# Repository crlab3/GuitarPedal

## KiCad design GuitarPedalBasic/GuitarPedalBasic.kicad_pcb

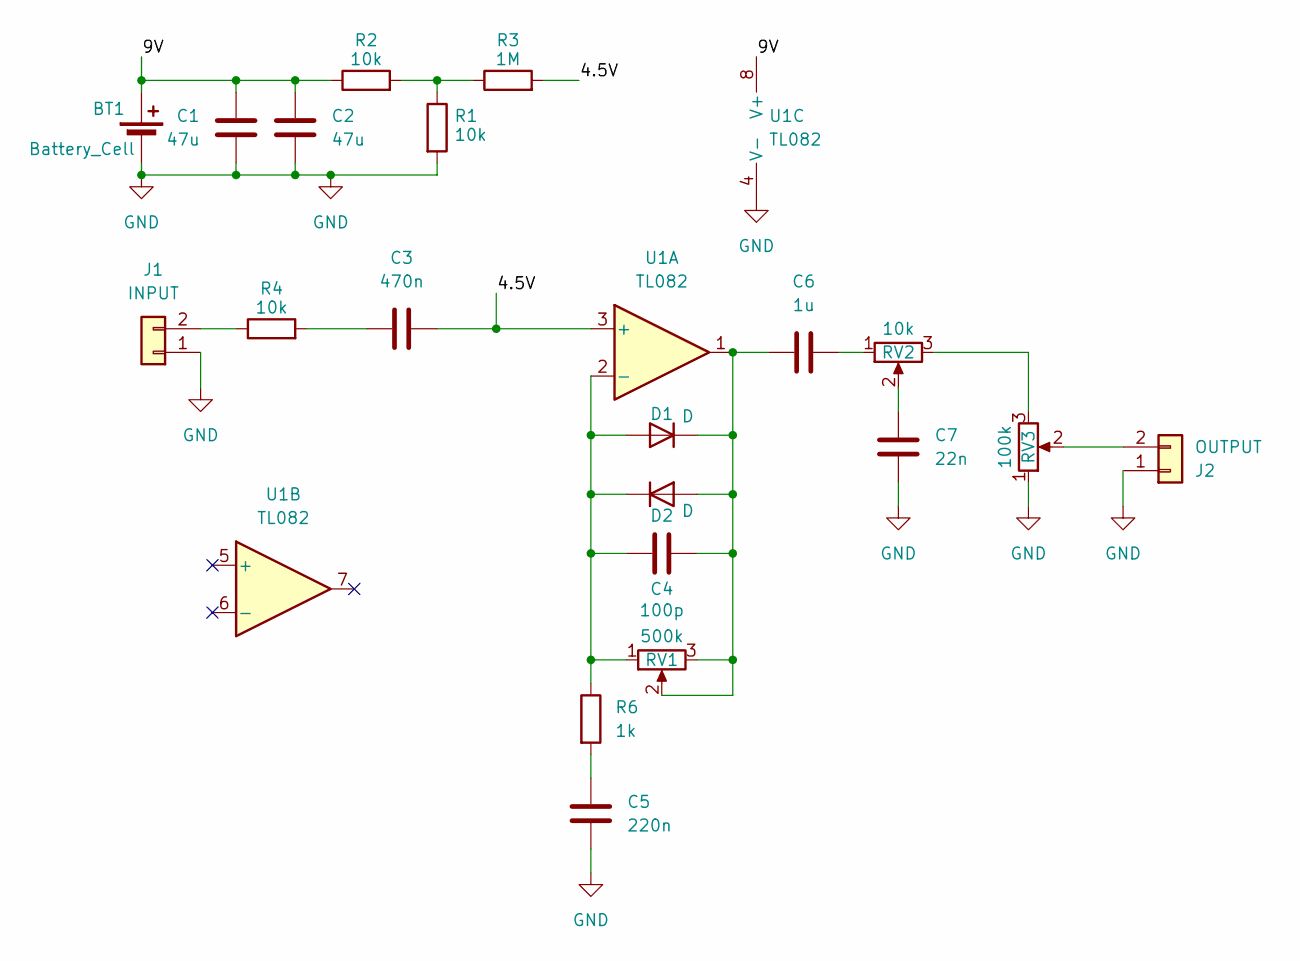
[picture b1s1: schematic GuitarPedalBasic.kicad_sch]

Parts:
BT1: Battery_Cell; TerminalBlock_4Ucon_1x02_P3.50mm_Horizontal
C1, C2: 47u; C_Elec_5x5.4
C3: 470n; C_0805_2012Metric
C4: 100p; C_0805_2012Metric
C5: 220n; C_0805_2012Metric
C6: 1u; C_0805_2012Metric
C7: 22n; C_0805_2012Metric
D1, D2: D; D_SMA
J1: INPUT; TerminalBlock_4Ucon_1x02_P3.50mm_Horizontal
J2: OUTPUT; TerminalBlock_4Ucon_1x02_P3.50mm_Horizontal
R1, R2, R4: 10k; R_0805_2012Metric
R3: 1M; R_0805_2012Metric
R6: 1k; R_0805_2012Metric
RV1: 500k; Potentiometer_Bourns_PTV09A-1_Single_Vertical; Mouser 652-PTV09A-4020FB504
RV2: 10k; Potentiometer_Bourns_PTV09A-1_Single_Vertical; Mouser 652-PTV09A4030FB103
RV3: 100k; Potentiometer_Bourns_PTV09A-1_Single_Vertical; Mouser 652-PTV09A-2025UA104
U1: TL082; SO-8_3.9x4.9mm_P1.27mm

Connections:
/4.5V: C3.2, R3.2, U1.3 (+)
/9V: BT1.1 (+), C1.1, C2.1, R2.1, U1.8 (V+)
GND: BT1.2 (-), C1.2, C2.2, C5.2, C7.1, J1.1, J2.1, R1.2, RV3.1, U1.4 (V-)
unnamed: C3.1, R4.2
unnamed: C5.1, R6.2
unnamed: C6.2, RV2.1
unnamed: C7.2, RV2.2
unnamed: C4.1, D1.2 (A), D2.1 (K), R6.1, RV1.1, U1.2 (-)
unnamed: C4.2, C6.1, D1.1 (K), D2.2 (A), RV1.2, RV1.3, U1.1
unnamed: J1.2, R4.1
unnamed: J2.2, RV3.2
unnamed: R1.1, R2.2, R3.1
unnamed: RV2.3, RV3.3

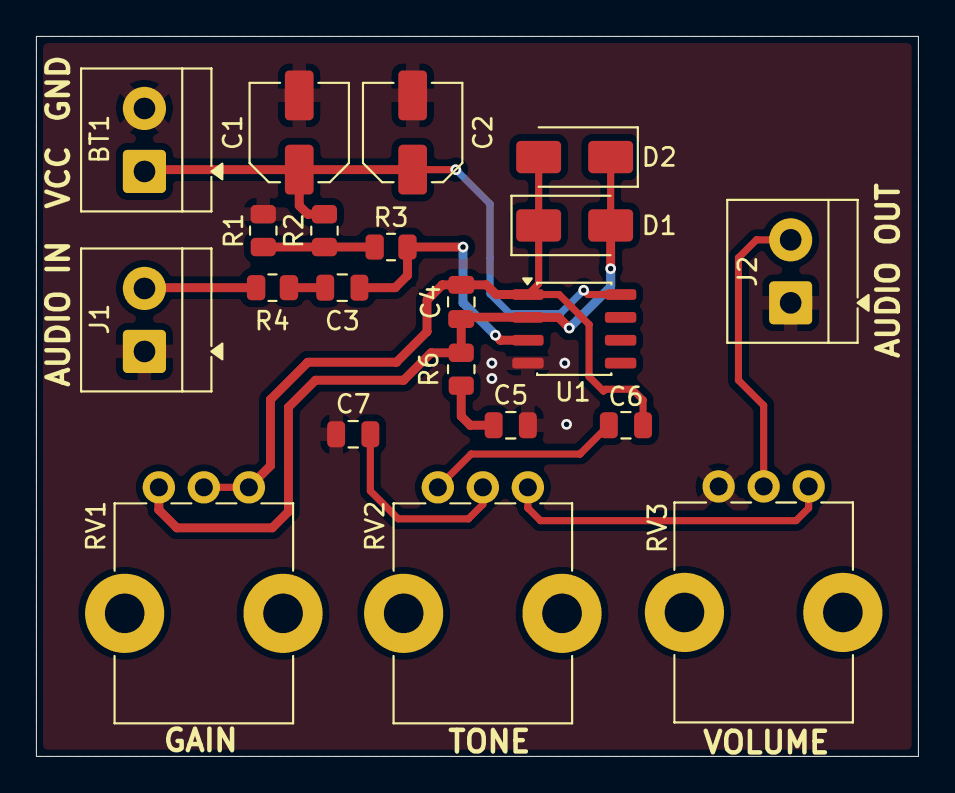
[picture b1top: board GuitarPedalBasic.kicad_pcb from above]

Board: 2 copper layers, 49.0 x 40.0 mm, 21 parts (0 on the bottom side), 13 nets.

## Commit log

2026-04-10 PCB widthout wires
2026-04-10 removebackups
2026-04-16 Without Tracks
2026-04-16 Added Tracks
2026-04-16 PCB With SilkScreen Text
2026-04-16 Done, BOM, MouserBasket
2026-04-16 some cleanup
2026-05-27 Simulations added
